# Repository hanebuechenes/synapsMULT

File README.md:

# synapsMULT — Buffered Multiple with Input Level LEDs

`synapsMULT` ist ein 4-Kanal Eurorack-Verteiler (Buffered Multiple) im Open-Source-Hardware-Format. Es verarbeitet sowohl Audio- als auch Steuerspannungssignale (CV) präzise und verlustfrei. 

Dank der internen Kaskadierung (Daisy-Chaining) lässt sich das Modul extrem flexibel als 1-zu-12, zweimal 1-zu-6 oder viermal 1-zu-3 Mult nutzen. Integrierte bipolare LEDs an jedem Kanal bieten eine direkte visuelle Pegelanzeige.

---

## Key Features

* **4 Unabhängige Buffer:** Basierend auf dem op-amp Klassiker TL074.
* **1-to-12 Normalisierung:** Kaskadierte Klinkenbuchsen schalten das Signal automatisch von `IN1` auf alle Kanäle durch, solange keine weiteren Eingänge belegt sind.
* **Visual Level Indication:** Bipolare LEDs (Rot/Grün) pro Eingang zeigen Signalpegel, Polarität (CV) und Dynamik (Audio) in Echtzeit an.
* **Saubere Entkopplung:** $1\text{k}\Omega$ Schutzwiderstände an allen Ausgängen zur Impedanzanpassung und Schutz vor Kurzschlüssen.
* **Low Component Count:** Einfach aufzubauen, ideal für DIY-Einsteiger und präzise genug für Pitch-CV.

---

## Module Overview

| Kanal | Eingang | Normalisiert von | Ausgänge | Status-LED |
| :--- | :--- | :--- | :--- | :--- |
| **Kanal 1** | IN1 | — | OUT1, OUT2, OUT3 | D3 |
| **Kanal 2** | IN2 | IN1 | OUT1, OUT2, OUT3 | D4 |
| **Kanal 3** | IN3 | IN2 | OUT1, OUT2, OUT3 | D5 |
| **Kanal 4** | IN4 | IN3 | OUT1, OUT2, OUT3 | D6 |

---

## Technical Specifications

* **Format:** Eurorack Modul
* **Versorgungsspannung:** $\pm12\text{V}$ (Standard Eurorack Power Ribbon Connector)
* **Op-Amp:** 1x TL074 Quad Operational Amplifier
* **LED-Vorwiderstände:** $3.3\text{k}\Omega$ für bipolare LEDs
* **Ausgangswiderstände:** $1\text{k}\Omega$ (Metallschicht 1%)

---

## Project Structure

```text
.
├── hardware/            # KiCad Schaltplan & PCB-Layout (.kicad_sch, .kicad_pcb)
├── gerbers/             # Produktionsdateien für PCB-Fertigung (JLCPCB ready)
├── docs/                # Bestückungsplan, BOM & Grafiken
├── LICENSE              # Lizenzdateien
└── README.md            # Projekt-Dokumentation

## License

Dieses Projekt ist unter den folgenden Open-Source-Lizenzen veröffentlicht:

    Hardware (Schaltplan & Layout): CERN OHL-P-2.0 (CERN Open Hardware Licence Permissive)

    Dokumentation: MIT License

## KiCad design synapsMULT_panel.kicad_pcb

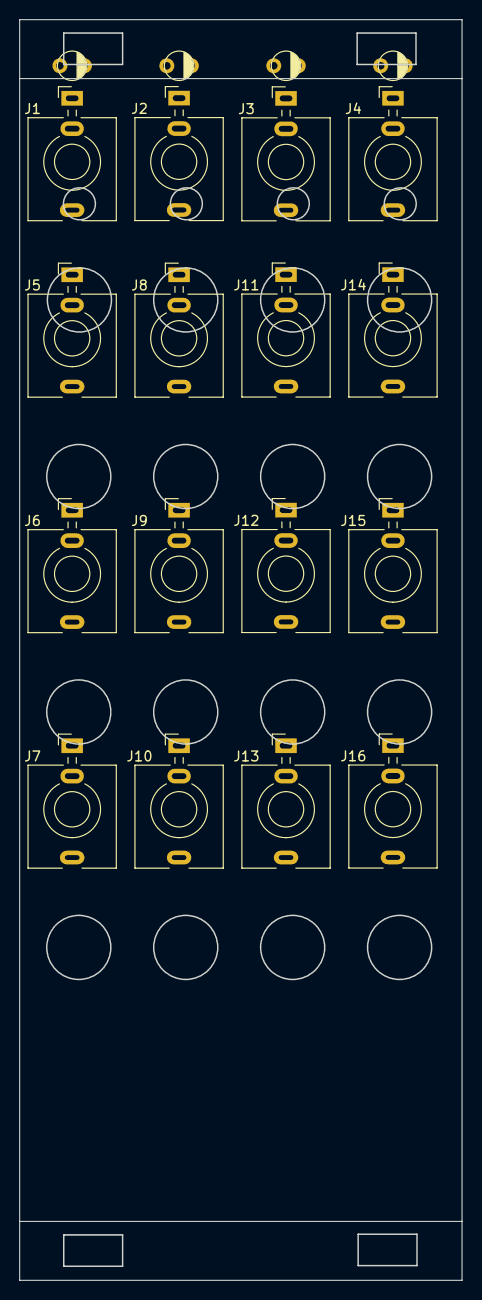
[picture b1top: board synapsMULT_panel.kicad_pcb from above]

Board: 2 copper layers, 45.1 x 128.5 mm, 20 parts (0 on the bottom side), 4 nets, no tracks yet.

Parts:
D3, D4, D5, D6: LED_Dual_Bidirectional; led-3mm
J1: IN1; 3.5mm_tip_switch_thonkiconn
J2: IN2; 3.5mm_tip_switch_thonkiconn
J3: IN3; 3.5mm_tip_switch_thonkiconn
J4: IN4; 3.5mm_tip_switch_thonkiconn
J5, J8, J11, J14: OUT1; 3.5mm_tip_switch_thonkiconn
J6, J9, J12, J15: OUT2; 3.5mm_tip_switch_thonkiconn
J7, J10, J13, J16: OUT3; 3.5mm_tip_switch_thonkiconn

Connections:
GND: J1.S, J2.S, J3.S, J4.S, J5.S, J6.S, J7.S, J8.S, J9.S, J10.S, J11.S, J12.S, J13.S, J14.S, J15.S, J16.S
unnamed: J1.T, J2.TN
unnamed: J3.T, J4.TN
unnamed: J2.T, J3.TN

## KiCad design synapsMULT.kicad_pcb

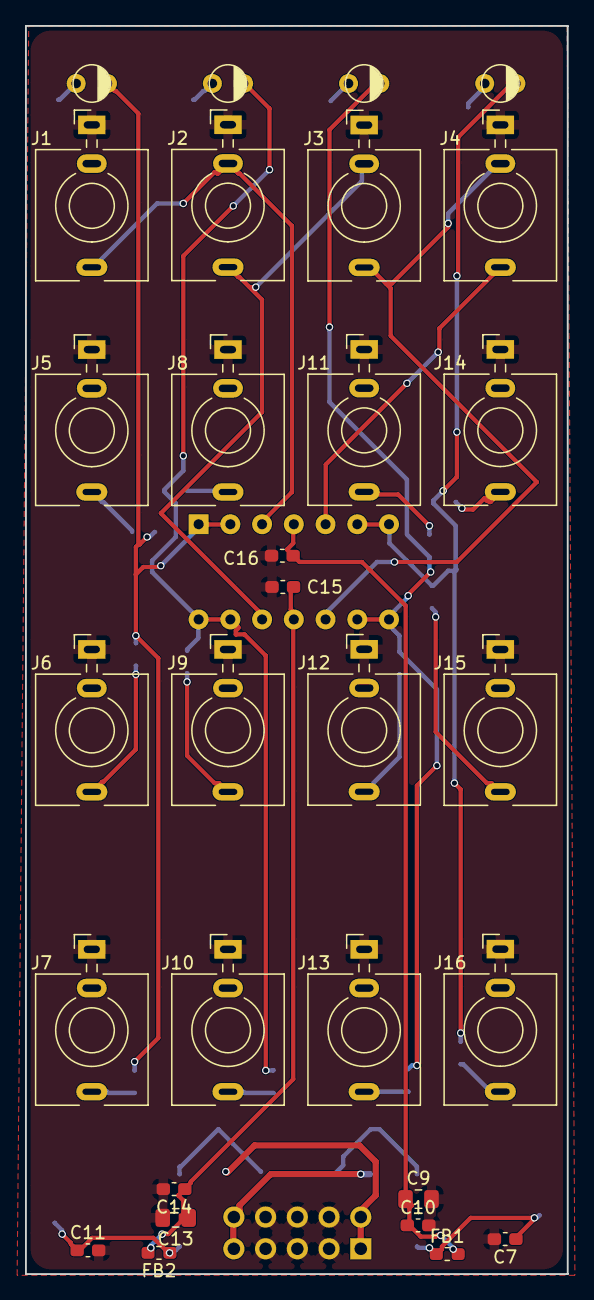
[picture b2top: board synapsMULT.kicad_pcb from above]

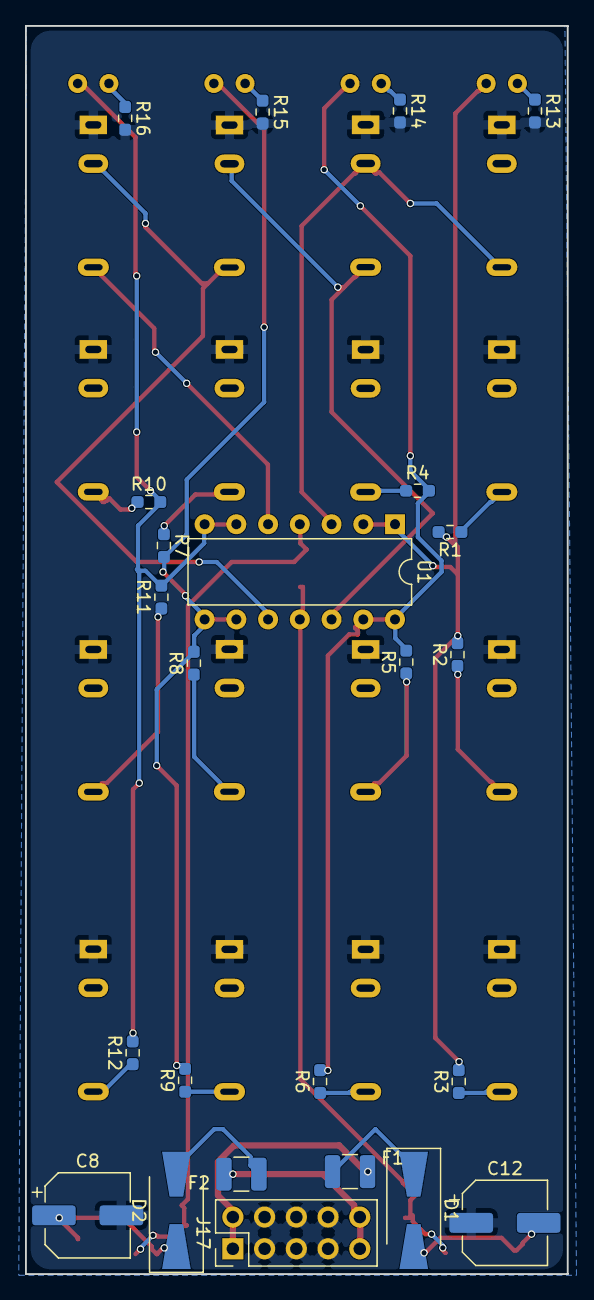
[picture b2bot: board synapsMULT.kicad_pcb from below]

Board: 2 copper layers, 43.4 x 99.9 mm, 54 parts (24 on the bottom side), 33 nets.

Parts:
C7, C10, C11, C14, C15, C16: 100nF 50V X7R; C_0603_1608Metric_Pad1.08x0.95mm_HandSolder
C8, C12: 100uF 25V; CP_Elec_6.3x7.7
C9, C13: 10uF 25V X7R; C_0805_2012Metric_Pad1.18x1.45mm_HandSolder
D1, D2: MBRA140T3G; D_SMA-SMB_Universal_Handsoldering
D3, D4, D5, D6: LED_Dual_Bidirectional; led-3mm
F1, F2: Polyfuse; Fuse_1210_3225Metric
FB1, FB2: 120R@100MHz 2A; L_0603_1608Metric_Pad1.05x0.95mm_HandSolder
J1: IN1; 3.5mm_tip_switch_thonkiconn
J2: IN2; 3.5mm_tip_switch_thonkiconn
J3: IN3; 3.5mm_tip_switch_thonkiconn
J4: IN4; 3.5mm_tip_switch_thonkiconn
J5, J8, J11, J14: OUT1; 3.5mm_tip_switch_thonkiconn
J6, J9, J12, J15: OUT2; 3.5mm_tip_switch_thonkiconn
J7, J10, J13, J16: OUT3; 3.5mm_tip_switch_thonkiconn
J17: Eurorack Header; PinHeader_2x05_P2.54mm_Vertical
R1, R2, R3, R4, R5, R6, R7, R8, R9, R10, R11, R12: 1k; R_0603_1608Metric_Pad0.98x0.95mm_HandSolder
R13, R14, R15, R16: 3,3k; R_0603_1608Metric_Pad0.98x0.95mm_HandSolder
U1: TL074; DIP-14_W7.62mm

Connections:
+12V: F2.1, J17.9, J17.10
+12VA: C9.1, C10.1, C16.1, FB1.2, U1.4 (V+)
+12V_RAW: C7.1, C8.1, D2.1 (K), FB1.1
-12V: F1.1, J17.1, J17.2
-12VA: C13.1, C14.1, C15.1, FB2.2, U1.11 (V-)
-12V_RAW: C11.1, C12.2, D1.2 (A), FB2.1
GND: C7.2, C8.2, C9.2, C10.2, C11.2, C12.1, C13.2, C14.2, C15.2, C16.2, J1.S, J2.S, J3.S, J4.S, J5.S, J6.S, J7.S, J8.S, J9.S, J10.S, J11.S, J12.S, J13.S, J14.S, J15.S, J16.S, J17.3, J17.4, J17.5, J17.6, J17.7, J17.8, R13.2, R14.2, R15.2, R16.2
unnamed: D1.1 (K), F1.2
unnamed: D2.2 (A), F2.2
unnamed: D3.2 (AK), R13.1
unnamed: D3.1 (KA), R1.2, R2.2, R3.2, U1.1, U1.2 (-)
unnamed: D4.2 (AK), R14.1
unnamed: D4.1 (KA), R4.2, R5.2, R6.2, U1.13 (-), U1.14
unnamed: D5.2 (AK), R15.1
unnamed: D5.1 (KA), R7.2, R8.2, R9.2, U1.8, U1.9 (-)
unnamed: D6.2 (AK), R16.1
unnamed: D6.1 (KA), R10.2, R11.2, R12.2, U1.6 (-), U1.7
unnamed: J5.T, R1.1
unnamed: J6.T, R2.1
unnamed: J7.T, R3.1
unnamed: J8.T, R4.1
unnamed: J9.T, R5.1
unnamed: J10.T, R6.1
unnamed: J11.T, R7.1
unnamed: J12.T, R8.1
unnamed: J13.T, R9.1
unnamed: J14.T, R10.1
unnamed: J15.T, R11.1
unnamed: J16.T, R12.1
unnamed: J1.T, J2.TN, U1.3 (+)
unnamed: J4.T, U1.5 (+)
unnamed: J3.T, J4.TN, U1.10 (+)
unnamed: J2.T, J3.TN, U1.12 (+)

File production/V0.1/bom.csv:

Designator,Footprint,Quantity,Value,LCSC Part #
"C10, C11, C14, C15, C16, C7",0603,6,100nF 50V X7R,
"C12, C8",CP_Elec_6.3x7.7,2,100uF 25V,
"C13, C9",0805,2,10uF 25V X7R,
"D1, D2",D_SMA-SMB_Universal_Handsoldering,2,MBRA140T3G,
"D3, D4, D5, D6",led-3mm,4,LED_Dual_Bidirectional,
"F1, F2",1210,2,Polyfuse,
"FB1, FB2",0603,2,120R@100MHz 2A,
J1,3.5mm_tip_switch_thonkiconn,1,IN1,
"J10, J13, J16, J7",3.5mm_tip_switch_thonkiconn,4,OUT3,
"J11, J14, J5, J8",3.5mm_tip_switch_thonkiconn,4,OUT1,
"J12, J15, J6, J9",3.5mm_tip_switch_thonkiconn,4,OUT2,
J17,PinHeader_2x05_P2.54mm_Vertical,1,Eurorack Header,
J2,3.5mm_tip_switch_thonkiconn,1,IN2,
J3,3.5mm_tip_switch_thonkiconn,1,IN3,
J4,3.5mm_tip_switch_thonkiconn,1,IN4,
"R1, R10, R11, R12, R2, R3, R4, R5, R6, R7, R8, R9",0603,12,1k,
"R13, R14, R15, R16",0603,4,"3,3k",
U1,DIP-14_W7.62mm,1,TL074,
